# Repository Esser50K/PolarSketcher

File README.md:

# Polar Sketcher

The polar Sketcher is a somewhat compact robotic arm plotter.

The motivation is to have a somewhat simple and cheap design to create a 2D plotter.
It is also meant to not occupy a lot of space when idle as you don't need an entire XY CNC setup.

## Demo Video

Take a look a the journey of this build (without looking at commits)
https://youtu.be/corrBt9IMOM

## Upload PolarSketcherFirmware

The firmware of this project is designed to run on an esp32.
To upload the code from the command line run the following command from the `PolarSketcherFirmware` directory:
> platformio run --target upload --environment uno

You may want to change the `serial_port` option in the `platformio.ini` file. The current one is meant for the raspberrypi when using the GPIO serial connection.

To download platformio in the first place run:

`
curl -fsSL
     -o get-platformio.py
     https://raw.githubusercontent.com/platformio/platformio-core-installer/master/get-platformio.py
`

`python3 get-platformio.py`

## Optional software

There is a feature still in development to allow for the storing of drawings in order to pick up where you left off.
for this a local mongoDB is needed, for development se this to run mongodb locally:
> docker run -p 27017:27017 -v $PWD/mongodb:/data/db mongo:latest

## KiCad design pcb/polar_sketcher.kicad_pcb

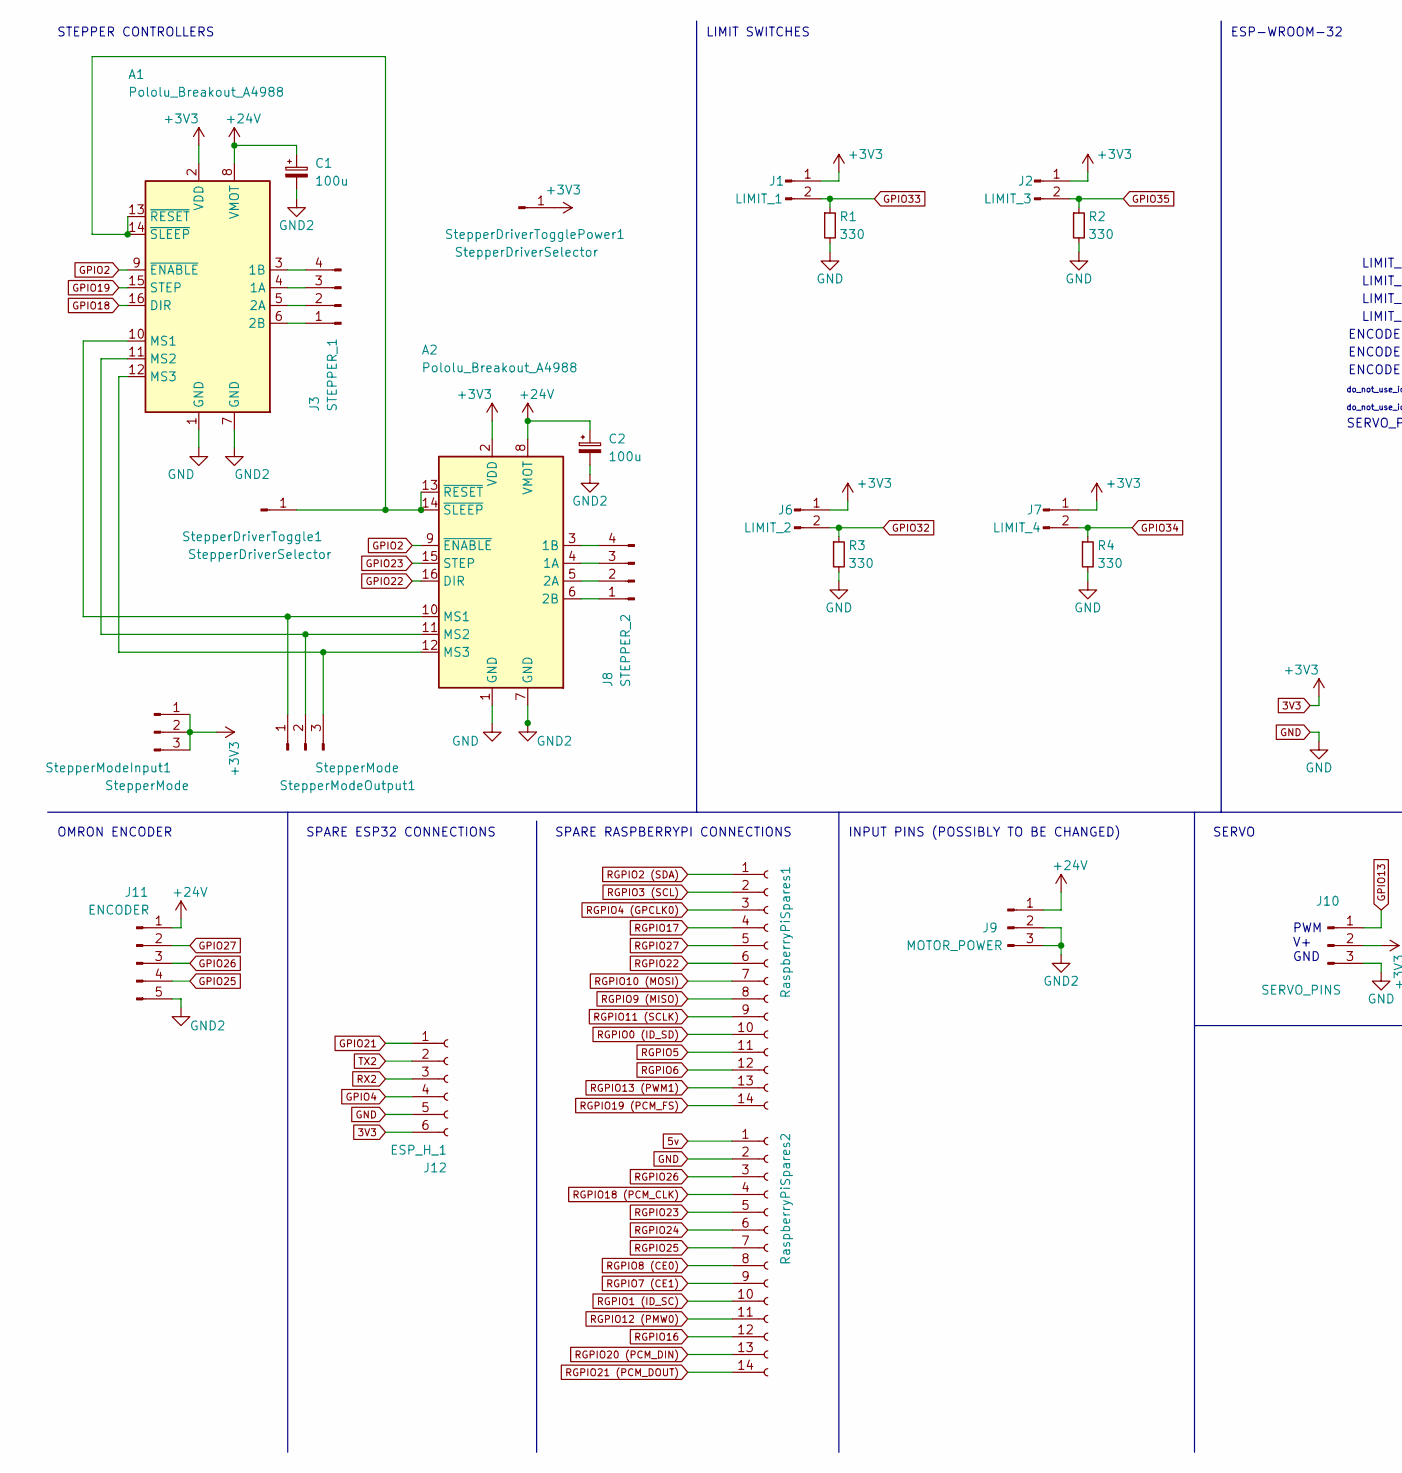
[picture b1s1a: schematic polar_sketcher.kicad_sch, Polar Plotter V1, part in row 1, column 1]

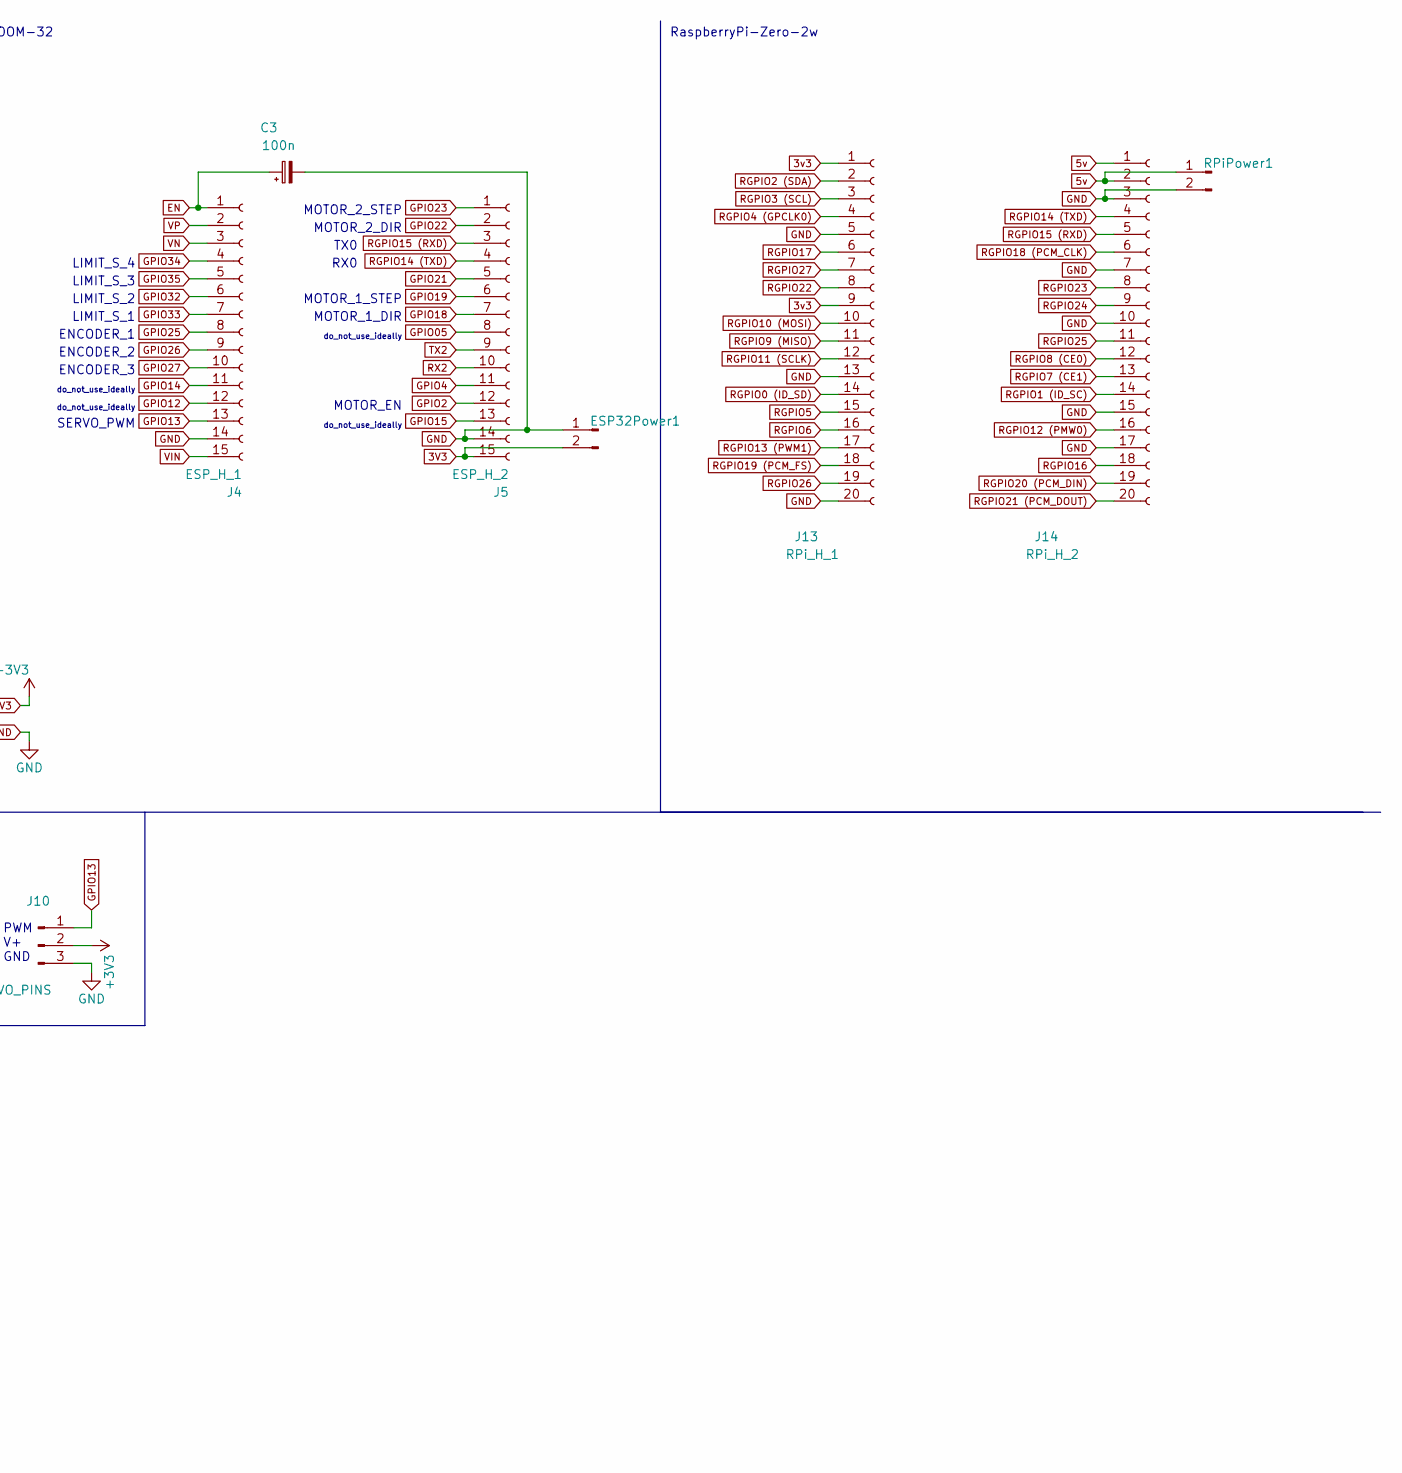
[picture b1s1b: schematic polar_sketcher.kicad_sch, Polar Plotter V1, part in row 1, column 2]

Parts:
A1, A2: Pololu_Breakout_A4988; Pololu_Breakout-16_15.2x20.3mm
C1, C2: 100u; CP_Radial_D8.0mm_P5.00mm
C3: 100n; CP_Radial_D4.0mm_P2.00mm
ESP32Power1: V+; PinHeader_1x02_P2.54mm_Vertical
J1: LIMIT_1; PinHeader_1x02_P2.54mm_Vertical
J2: LIMIT_3; PinHeader_1x02_P2.54mm_Vertical
J3: STEPPER_1; PinHeader_1x04_P2.54mm_Vertical
J4: ESP_H_1; PinSocket_1x15_P2.54mm_Vertical
J5: ESP_H_2; PinSocket_1x15_P2.54mm_Vertical
J6: LIMIT_2; PinHeader_1x02_P2.54mm_Vertical
J7: LIMIT_4; PinHeader_1x02_P2.54mm_Vertical
J8: STEPPER_2; PinHeader_1x04_P2.54mm_Vertical
J9: MOTOR_POWER; PinHeader_1x03_P2.54mm_Vertical
J10: SERVO_PINS; PinHeader_1x03_P2.54mm_Vertical
J11: ENCODER; PinHeader_1x05_P2.54mm_Vertical
J12: ESP_H_1; PinSocket_1x06_P2.54mm_Vertical
J13: RPi_H_1; PinSocket_1x20_P2.54mm_Vertical
J14: RPi_H_2; PinSocket_1x20_P2.54mm_Vertical
R1, R2, R3, R4: 330; R_Axial_DIN0207_L6.3mm_D2.5mm_P7.62mm_Horizontal
RPiPower1: V+; PinHeader_1x02_P2.54mm_Vertical
RaspberryPiSpares1, RaspberryPiSpares2: RPi_H_1; PinSocket_1x14_P2.54mm_Vertical
StepperDriverToggle1: StepperDriverSelector; PinHeader_1x01_P2.54mm_Vertical
StepperDriverTogglePower1: StepperDriverSelector; PinHeader_1x01_P2.54mm_Vertical
StepperModeInput1: StepperMode; PinHeader_1x03_P2.54mm_Vertical
StepperModeOutput1: StepperMode; PinHeader_1x03_P2.54mm_Vertical

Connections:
3V3: A1.2 (VDD), A2.2 (VDD), ESP32Power1.2, J1.1, J2.1, J5.15, J6.1, J7.1, J10.2, J12.6, StepperDriverTogglePower1.1, StepperModeInput1.1, StepperModeInput1.2, StepperModeInput1.3
3v3: J13.1, J13.9
5v: J14.1, J14.2, RPiPower1.1, RaspberryPiSpares2.1
+24V: A1.8 (VMOT), A2.8 (VMOT), C1.1, C2.1, J9.1, J11.1
EN: C3.1, J4.1
GND: A1.1 (GND), A2.1 (GND), C3.2, ESP32Power1.1, J4.14, J5.14, J10.3, J12.5, J13.5, J13.13, J13.20, J14.3, J14.7, J14.10, J14.15, J14.17, R1.2, R2.2, R3.2, R4.2, RPiPower1.2, RaspberryPiSpares2.2
GND2: A1.7 (GND), A2.7 (GND), C1.2, C2.2, J9.2, J9.3, J11.5
GPIO2: A1.9 (~ENABLE), A2.9 (~ENABLE), J5.12
GPIO4: J5.11, J12.4
GPIO05: J5.8
GPIO12: J4.12
GPIO13: J4.13, J10.1
GPIO14: J4.11
GPIO15: J5.13
GPIO18: A1.16 (DIR), J5.7
GPIO19: A1.15 (STEP), J5.6
GPIO21: J5.5, J12.1
GPIO22: A2.16 (DIR), J5.2
GPIO23: A2.15 (STEP), J5.1
GPIO25: J4.8, J11.4
GPIO26: J4.9, J11.3
GPIO27: J4.10, J11.2
GPIO32: J4.6, J6.2, R3.1
GPIO33: J1.2, J4.7, R1.1
GPIO34: J4.4, J7.2, R4.1
GPIO35: J2.2, J4.5, R2.1
unnamed: A1.3 (1B), J3.4
unnamed: A1.4 (1A), J3.3
unnamed: A1.5 (2A), J3.2
unnamed: A1.6 (2B), J3.1
unnamed: A1.10 (MS1), A2.10 (MS1), StepperModeOutput1.1
unnamed: A1.11 (MS2), A2.11 (MS2), StepperModeOutput1.2
unnamed: A1.12 (MS3), A2.12 (MS3), StepperModeOutput1.3
unnamed: A1.13 (~RESET), A1.14 (~SLEEP), A2.13 (~RESET), A2.14 (~SLEEP), StepperDriverToggle1.1
unnamed: A2.3 (1B), J8.4
unnamed: A2.4 (1A), J8.3
unnamed: A2.5 (2A), J8.2
unnamed: A2.6 (2B), J8.1
RGPIO0 (ID_SD): J13.14, RaspberryPiSpares1.10
RGPIO1 (ID_SC): J14.14, RaspberryPiSpares2.10
RGPIO2 (SDA): J13.2, RaspberryPiSpares1.1
RGPIO3 (SCL): J13.3, RaspberryPiSpares1.2
RGPIO4 (GPCLK0): J13.4, RaspberryPiSpares1.3
RGPIO5: J13.15, RaspberryPiSpares1.11
RGPIO6: J13.16, RaspberryPiSpares1.12
RGPIO7 (CE1): J14.13, RaspberryPiSpares2.9
RGPIO8 (CE0): J14.12, RaspberryPiSpares2.8
RGPIO9 (MISO): J13.11, RaspberryPiSpares1.8
RGPIO10 (MOSI): J13.10, RaspberryPiSpares1.7
RGPIO11 (SCLK): J13.12, RaspberryPiSpares1.9
RGPIO12 (PMW0): J14.16, RaspberryPiSpares2.11
RGPIO13 (PWM1): J13.17, RaspberryPiSpares1.13
RGPIO14 (TXD): J5.4, J14.4
RGPIO15 (RXD): J5.3, J14.5
RGPIO16: J14.18, RaspberryPiSpares2.12
RGPIO17: J13.6, RaspberryPiSpares1.4
RGPIO18 (PCM_CLK): J14.6, RaspberryPiSpares2.4
RGPIO19 (PCM_FS): J13.18, RaspberryPiSpares1.14
RGPIO20 (PCM_DIN): J14.19, RaspberryPiSpares2.13
RGPIO21 (PCM_DOUT): J14.20, RaspberryPiSpares2.14
RGPIO22: J13.8, RaspberryPiSpares1.6
RGPIO23: J14.8, RaspberryPiSpares2.5
RGPIO24: J14.9, RaspberryPiSpares2.6
RGPIO25: J14.11, RaspberryPiSpares2.7
RGPIO26: J13.19, RaspberryPiSpares2.3
RGPIO27: J13.7, RaspberryPiSpares1.5
RX2: J5.10, J12.3
TX2: J5.9, J12.2
VIN: J4.15
VN: J4.3
VP: J4.2

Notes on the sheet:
do_not_use_ideally
SPARE ESP32 CONNECTIONS
MOTOR_2_STEP
LIMIT_S_2
RaspberryPi-Zero-2w
TX0
LIMIT_S_4
MOTOR_1_STEP
ENCODER_3
MOTOR_EN
LIMIT SWITCHES
OMRON ENCODER
MOTOR_1_DIR
ENCODER_2
SERVO_PWM
SERVO
ESP-WROOM-32
ENCODER_1
STEPPER CONTROLLERS
SPARE RASPBERRYPI CONNECTIONS
MOTOR_2_DIR
PWM V+ GND
LIMIT_S_1
RX0
LIMIT_S_3
INPUT PINS (POSSIBLY TO BE CHANGED)

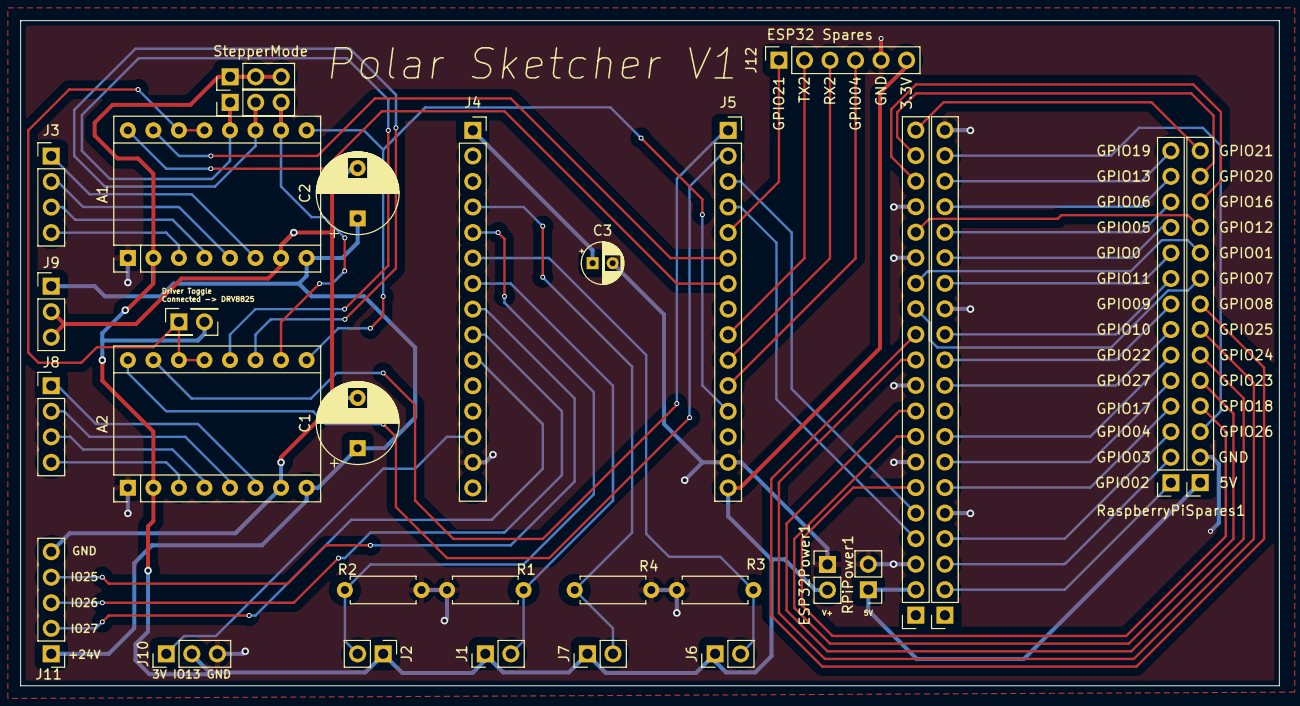
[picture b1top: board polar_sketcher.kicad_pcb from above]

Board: 2 copper layers, 125.2 x 66.2 mm, 31 parts (0 on the bottom side), 64 nets.

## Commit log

2021-07-25 adds minimal UI and README
2021-08-30 adds simulator and fullstack simulator code
2021-09-03 streams progress simulation to the browser
2021-09-04 fixes simulator and removes pygame from server and adds slider
2021-09-05 uses thread instead of process and fixes a blocking issue in the BE
2021-09-10 adds path sorting algorithms to choose from
2021-09-10 WIP: toolpath algorithm
2021-09-13 implemented zigzag toolpath generation and fixed some bugs
2021-09-14 fixes a an issue in the toolpath generation by detecting if the intersected paths are the same for the next line
2021-09-19 fixes drawing when bbox is bigger than viewbox
2021-10-03 setting svglibs to point to repository directly in requirements.txt
2021-10-05 new toolpath generation algorithm
2021-10-14 integrates tailwind + fixes some UI bugs + little makeover
2021-10-15 adds maxout button and fixes a few more bugs
2021-10-16 implements ui design
2021-10-16 removes option for split parsing
2021-10-17 enables drawing with rotation
2021-10-22 fixes rendering size and rotation
2021-10-22 makes toolpath configurable from the UI
2021-10-22 makes path sorting algorithm configurable from the UI
2021-10-23 enables angling of the toolpath algorithm
2021-11-01 draws actual lines instead of dots on SimulationCanvas
2021-11-06 enables connecting to the physical polar sketcher
2022-11-07 major code cleanup and fixes all around
2022-11-07 remove experiments folder
2022-11-07 rename server.py to main.py
2022-11-19 major toolpath generation algorithms refactor using the quadtree
2023-02-17 adds PolarSketcherFirmware for esp32 created with Platformio
2023-02-23 fixes pen position bugs. Polar sketcher corrects angle position
2023-02-23 fixes not setting offset
2023-03-07 fix RX buffer overflow and pen not lifting when path is not closed
2023-03-20 fix couple bug and improve position correction
2023-03-20 adds labels of position and size of svg in canvas
2023-03-22 fix the position overflow problem; fix frontend illustration
2023-03-25 adjust measurements and add UI limits improvment
2023-03-26 fixes measurements and angle position correction, also improves accuracy by generating more points
2023-03-26 adds ability to see previously drawn paths
2023-03-27 add reduced mode implementation in UI
2023-04-02 implement drawing of boundary
2023-04-03 support for standard paper sizes and boundary drawing fix
2023-05-29 implement incremental error correction
2023-05-29 move to using line_step instead of n_lines
2023-06-04 represent limits for all supported canvas sizes
2023-06-05 resize drawnSVGs properly
2023-06-05 enables saving drawings to mongodb
2023-08-01 updates communication to be async
2023-08-05 error correction routine improvement. paths close properly
2023-08-13 clean up backend folder
2023-08-13 add missing ascii_utils.py file
2023-08-13 separate dev_requirements from others
2023-08-13 adds contour extraction experiment to experiments
2023-08-13 fix flask-sockets bug
2023-08-13 adds Dockerfiles for backend
2023-08-13 fix Dockerfile for raspberrypi and use opencv headless
2023-08-18 publish video link in README
2023-08-24 create Dockerfile for frontend
2023-09-02 fix bug in docker start CMD
2023-09-02 shorten the ACK messages + dynamic serial port finding
2023-09-02 fix path sort algorithm by using reversed() instead of reverse()
2023-09-02 fix build for raspberrypi
2023-09-02 fix incorrect opening of serial port
2023-09-07 get status when retry is needed
2023-09-09 make polar_sketcher_interface a global object
2023-09-16 makes polar sketcher only send 1 byte per loop at maximum, making the motors stall less and be more silent
2023-09-16 move quicker through intermediate points
2023-10-08 experimenting drawing with sin waves
2023-10-10 implemented connecting sin drawer
2023-10-12 implemented sin_drawer_along_path.py
2023-10-16 update react version and install new dependencies
2023-10-22 using drawing resolution param
2023-10-29 fixes setting square aspect ratio for all sizes
2023-10-30 better PolarSketcherInterface initialisation
2023-10-30 refactored drawing job
2023-10-30 separated drawing_job from job_manager
2023-10-30 integrated sin_along_path_drawer and bitmap processor cleanup
2023-10-31 integrated bitmap processors into UI
2023-10-31 fixes on polar_sketcher_consumer
2023-10-31 comitting missing bitmap processors
2023-10-31 setting condition in polar sketcher consumer to not lift pen if connecting path is close enough
2023-10-31 comitting missing firmware communicator
2023-10-31 comitting kicad pcb files
2023-10-31 updates gitignore
2023-10-31 optimizing bitmap processors to make use of generators
2023-10-31 lowering max_path_len of sin_wave processor
2023-10-31 optimising sine wave generator to generate points straight away
2023-10-31 fix bug in plotter communication
2023-11-01 remove waiting for startup message because raspberrypi always misses it
2023-11-01 pass arguments from ui to bitmap processors
2023-11-01 fix faulty int64_t type
2023-11-01 waits on setup done again, fixes bug of unnecessary pen lifting
2023-11-01 more rpi fixes
2023-11-01 more fixes
2023-11-01 adds --fix-missing to rpi Dockerfile
2023-11-01 fix rpi Dockerfile
2023-11-01 add important dependency for svgpathtools to calculate bezier curves efficiently
2023-11-02 more bugfixes in the polar_sketcher_consumer
2023-11-02 another bugfix, passing wrong type
2023-11-02 add an abort functionality
2023-11-03 parse sin wave args as floats
2023-11-03 make ws protocol and UI updates much more efficient
2023-11-05 generate paths in a thread, allowing the server thread to multiplex for efficiently. Fixes blocking on abort.
2023-11-05 add threaded approach to regular paths too, clean refactor of feature
2023-11-05 add feature to enable angle correction by config
2023-11-05 fixes bad parameter parsing
2023-11-05 fix early return bug in threaded path generation
2023-11-05 remove constant multiplier that slowed down path generation
2023-11-06 adds the constant multiplier back, movement was too jittery for plotter. more bug fixes.
2023-11-11 clean up the angle correction routine
2023-11-11 update calibration values
2023-11-12 uses a more chill angle correction algorithm
2023-11-12 change default threaded_generation queue size to avoid plotter from stopping
2023-11-21 add 'serial' as key prefix to look for in devices. Especially made for raspberrypi when communicating over GPIO pins
2023-11-22 add info on how to upload firmware directly from the raspberry pi
2023-11-22 small fixes in the enable motor logic
2023-11-26 add all models for current version of polar plotter
2023-12-02 fix design flaw in PCB that makes it fry the esp32 if you connect the encoder the opposite way around
2023-12-02 update calibration values with values from the drv8825 driver
2023-12-02 removing reset sequence because its not working on the new esp32
2023-12-03 new calibration values
2023-12-03 Revert "new calibration values"
    This reverts commit 4d135bc593fd306e36c73a562f358e138e867b85.
